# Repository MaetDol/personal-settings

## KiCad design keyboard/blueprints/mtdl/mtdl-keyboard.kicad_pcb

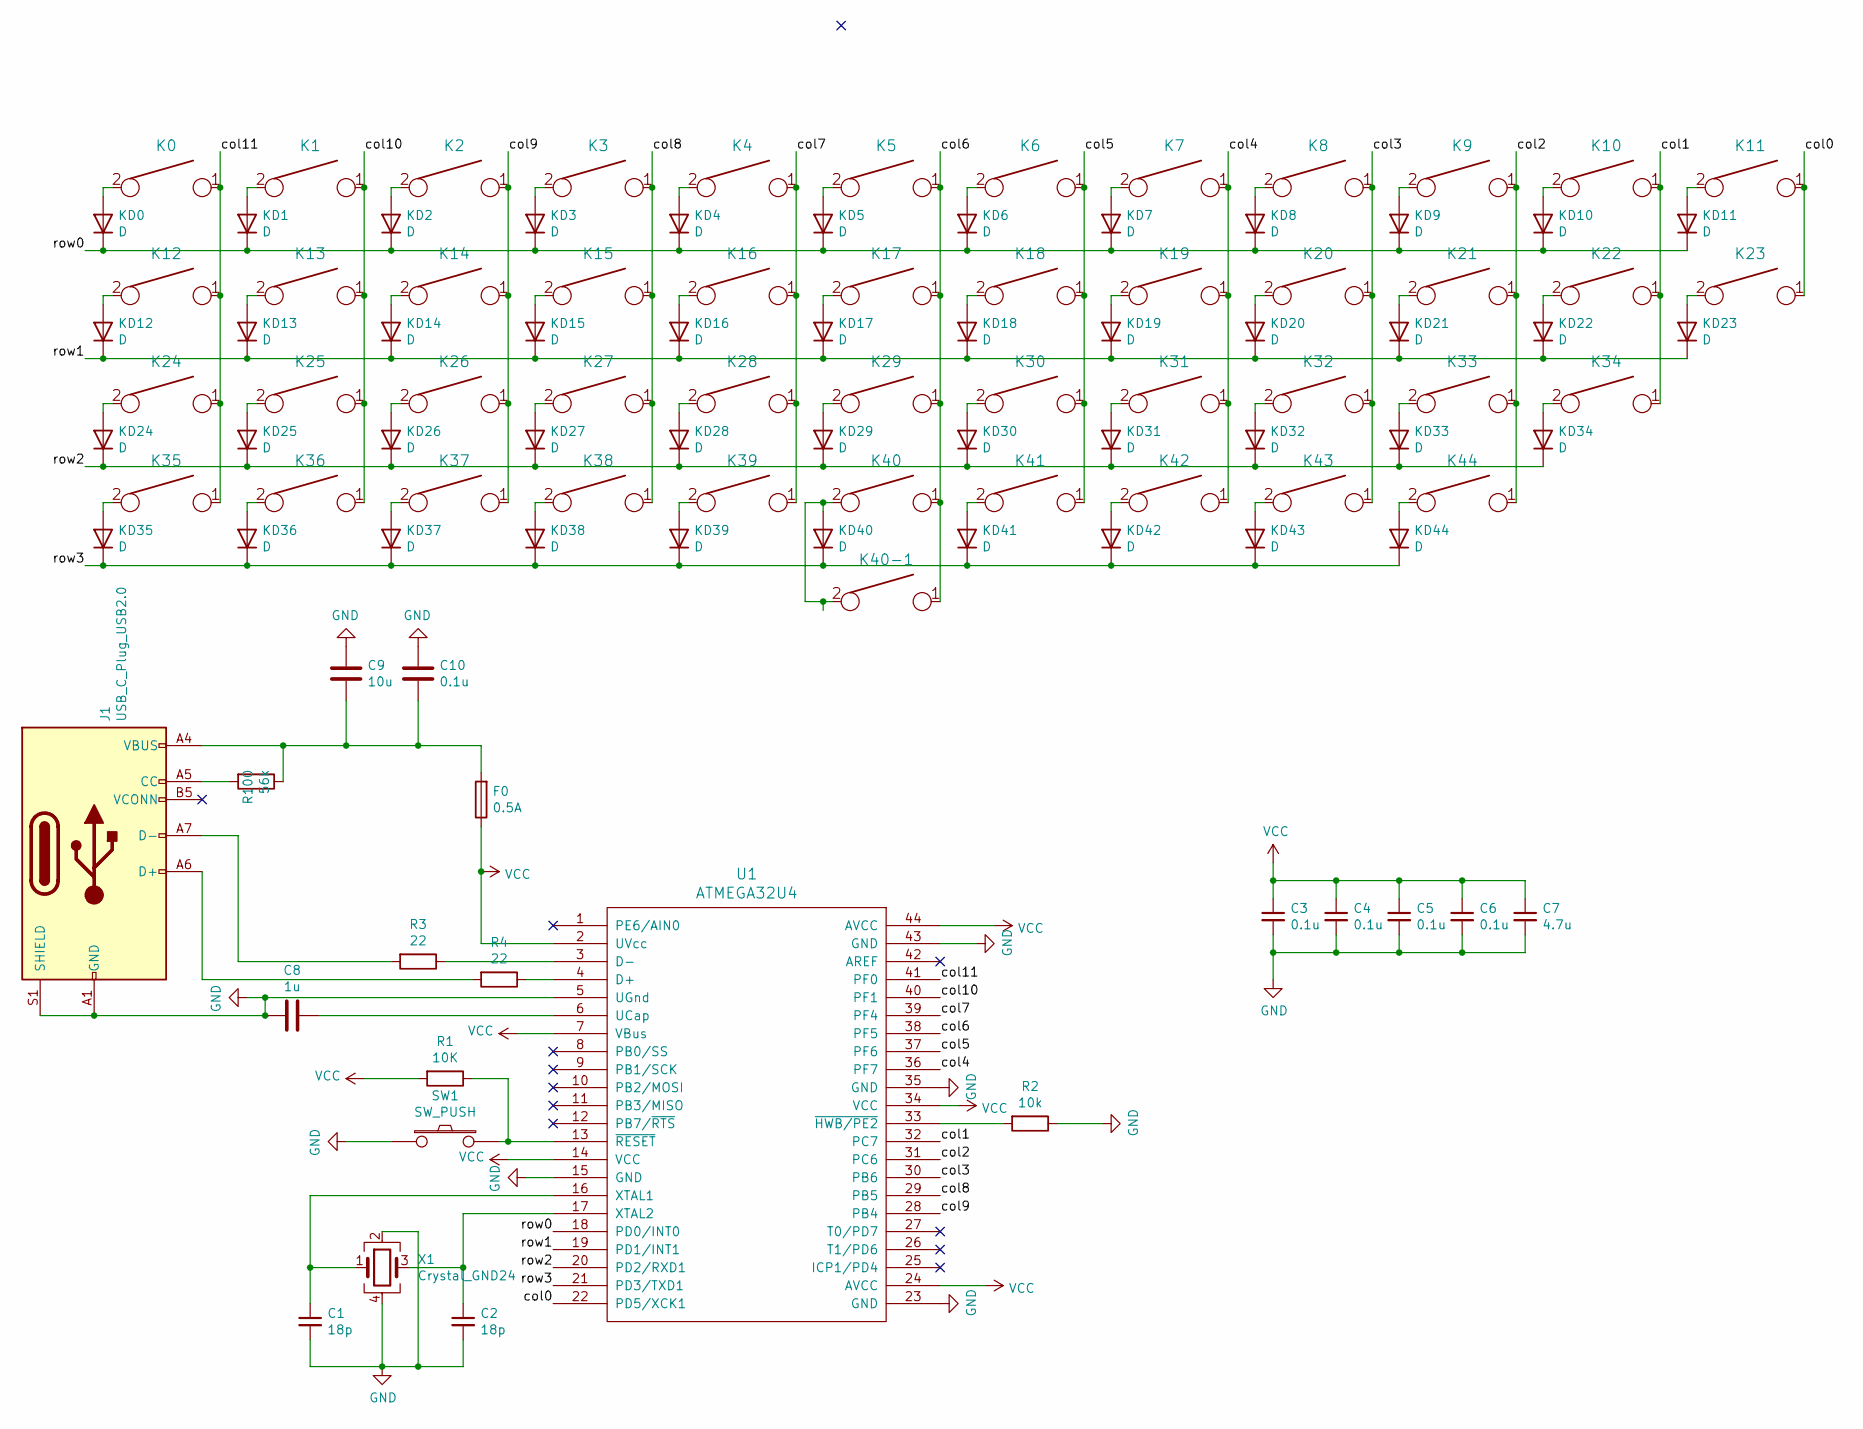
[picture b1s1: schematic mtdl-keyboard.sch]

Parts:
C1, C2: 18p; C_0805_2012Metric
C3, C4, C5, C6, C10: 0.1u; C_0805_2012Metric
C7: 4.7u; C_0805_2012Metric
C8: 1u; C_0805_2012Metric
C9: 10u; C_0805_2012Metric
F0: 0.5A; Fuse_0805_2012Metric
J1: USB_C_Plug_USB2.0; USB_C_Receptacle_Amphenol_12401548E4-2A
K0, K39, K40-1: KEYSW; Mx_Alps_200
K1, K2, K3, K4, K5, K6, K7, K8, K9, K10, K11, K13, K14, K15, K16, K17, K18, K19, K20, K21, K22, K25, K26, K27, K28, K29, K30, K31, K32, K33, K35, K37, K38, K42, K44: KEYSW; Mx_Alps_100
K12, K34: KEYSW; Mx_Alps_175
K23, K41, K43: KEYSW; Mx_Alps_125
K24: KEYSW; Mx_Alps_225
K36: KEYSW; Mx_Alps_150
K40: KEYSW; Mx_Alps_625
KD0, KD1, KD2, KD3, KD4, KD5, KD6, KD7, KD8, KD9, KD10, KD11, KD12, KD13, KD14, KD15, KD16, KD17, KD18, KD19, KD20, KD21, KD22, KD23, KD24, KD25, KD26, KD27, KD28, KD29, KD30, KD31, KD32, KD33, KD34, KD35, KD36, KD37, KD38, KD39, KD40, KD41, KD42, KD43, KD44: D; D_0805_2012Metric
R1: 10K; R_0805_2012Metric
R2: 10k; R_0805_2012Metric
R3, R4: 22; R_0805_2012Metric
R100: 56k; R_0805_2012Metric
SW1: SW_PUSH; SW_SPST_TL3342
U1: ATMEGA32U4; TQFP-44_10x10mm_P0.8mm
X1: Crystal_GND24; Crystal_SMD_TXC_7M-4Pin_3.2x2.5mm

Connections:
/col0: K0.1, K12.1, K24.1, K35.1, U1.41 (PF0)
/col1: K1.1, K13.1, K25.1, K36.1, U1.40 (PF1)
/col2: K2.1, K14.1, K26.1, K37.1, U1.28 (PB4)
/col3: K3.1, K15.1, K27.1, K38.1, U1.29 (PB5)
/col4: K4.1, K16.1, K28.1, K39.1, U1.39 (PF4)
/col5: K5.1, K17.1, K29.1, K40.1, K40-1.1, U1.38 (PF5)
/col6: K6.1, K18.1, K30.1, K41.1, U1.37 (PF6)
/col7: K7.1, K19.1, K31.1, K42.1, U1.36 (PF7)
/col8: K8.1, K20.1, K32.1, K43.1, U1.30 (PB6)
/col9: K9.1, K21.1, K33.1, K44.1, U1.31 (PC6)
/col10: K10.1, K22.1, K34.1, U1.32 (PC7)
/col11: K11.1, K23.1, U1.22 (PD5/XCK1)
/row0: KD0.1 (K), KD1.1 (K), KD2.1 (K), KD3.1 (K), KD4.1 (K), KD5.1 (K), KD6.1 (K), KD7.1 (K), KD8.1 (K), KD9.1 (K), KD10.1 (K), KD11.1 (K), U1.18 (PD0/INT0)
/row1: KD12.1 (K), KD13.1 (K), KD14.1 (K), KD15.1 (K), KD16.1 (K), KD17.1 (K), KD18.1 (K), KD19.1 (K), KD20.1 (K), KD21.1 (K), KD22.1 (K), KD23.1 (K), U1.19 (PD1/INT1)
/row2: KD24.1 (K), KD25.1 (K), KD26.1 (K), KD27.1 (K), KD28.1 (K), KD29.1 (K), KD30.1 (K), KD31.1 (K), KD32.1 (K), KD33.1 (K), KD34.1 (K), U1.20 (PD2/RXD1)
/row3: KD35.1 (K), KD36.1 (K), KD37.1 (K), KD38.1 (K), KD39.1 (K), KD40.1 (K), KD41.1 (K), KD42.1 (K), KD43.1 (K), KD44.1 (K), U1.21 (PD3/TXD1)
GND: C1.2, C2.2, C3.2, C4.2, C5.2, C6.2, C7.2, C8.2, C9.1, C10.1, J1.A1 (GND), J1.A12 (GND), J1.B1 (GND), J1.B12 (GND), J1.S1 (SHIELD), R2.1, SW1.1, U1.5 (UGnd), U1.15 (GND), U1.23 (GND), U1.35 (GND), U1.43 (GND), X1.2, X1.4
unnamed: C1.1, U1.16 (XTAL1), X1.1
unnamed: C2.1, U1.17 (XTAL2), X1.3
unnamed: C8.1, U1.6 (UCap)
unnamed: C9.2, C10.2, F0.2, J1.A4 (VBUS), J1.A9 (VBUS), J1.B4 (VBUS), J1.B9 (VBUS), R100.1
unnamed: J1.A5 (CC), R100.2
unnamed: J1.A6 (D+), R4.2
unnamed: J1.A7 (D-), R3.2
unnamed: K0.2, KD0.2 (A)
unnamed: K1.2, KD1.2 (A)
unnamed: K2.2, KD2.2 (A)
unnamed: K3.2, KD3.2 (A)
unnamed: K4.2, KD4.2 (A)
unnamed: K5.2, KD5.2 (A)
unnamed: K6.2, KD6.2 (A)
unnamed: K7.2, KD7.2 (A)
unnamed: K8.2, KD8.2 (A)
unnamed: K9.2, KD9.2 (A)
unnamed: K10.2, KD10.2 (A)
unnamed: K11.2, KD11.2 (A)
unnamed: K12.2, KD12.2 (A)
unnamed: K13.2, KD13.2 (A)
unnamed: K14.2, KD14.2 (A)
unnamed: K15.2, KD15.2 (A)
unnamed: K16.2, KD16.2 (A)
unnamed: K17.2, KD17.2 (A)
unnamed: K18.2, KD18.2 (A)
unnamed: K19.2, KD19.2 (A)
unnamed: K20.2, KD20.2 (A)
unnamed: K21.2, KD21.2 (A)
unnamed: K22.2, KD22.2 (A)
unnamed: K23.2, KD23.2 (A)
unnamed: K24.2, KD24.2 (A)
unnamed: K25.2, KD25.2 (A)
unnamed: K26.2, KD26.2 (A)
unnamed: K27.2, KD27.2 (A)
unnamed: K28.2, KD28.2 (A)
unnamed: K29.2, KD29.2 (A)
unnamed: K30.2, KD30.2 (A)
unnamed: K31.2, KD31.2 (A)
unnamed: K32.2, KD32.2 (A)
unnamed: K33.2, KD33.2 (A)
unnamed: K34.2, KD34.2 (A)
unnamed: K35.2, KD35.2 (A)
unnamed: K36.2, KD36.2 (A)
unnamed: K37.2, KD37.2 (A)
unnamed: K38.2, KD38.2 (A)
unnamed: K39.2, KD39.2 (A)
unnamed: K40.2, K40-1.2, KD40.2 (A)
unnamed: K41.2, KD41.2 (A)
unnamed: K42.2, KD42.2 (A)
unnamed: K43.2, KD43.2 (A)
unnamed: K44.2, KD44.2 (A)
unnamed: R1.1, SW1.2, U1.13 (~RESET)
unnamed: R2.2, U1.33 (~HWB/PE2)
unnamed: R3.1, U1.3 (D-)
unnamed: R4.1, U1.4 (D+)
VCC: C3.1, C4.1, C5.1, C6.1, C7.1, F0.1, R1.2, U1.2 (UVcc), U1.7 (VBus), U1.14 (VCC), U1.24 (AVCC), U1.34 (VCC), U1.44 (AVCC)

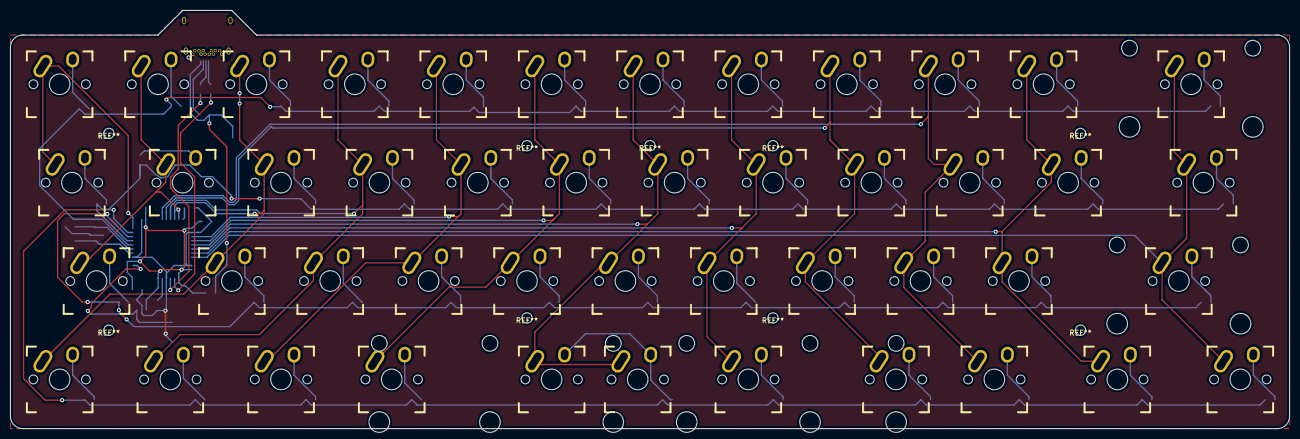
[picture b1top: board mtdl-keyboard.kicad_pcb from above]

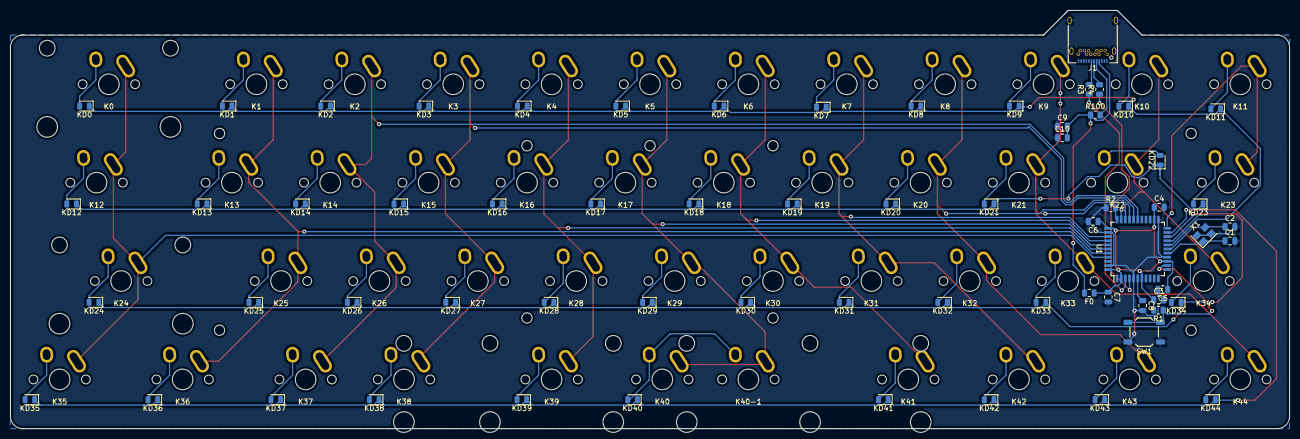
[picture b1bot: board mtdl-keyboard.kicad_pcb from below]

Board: 2 copper layers, 247.6 x 81.0 mm, 111 parts (65 on the bottom side), 74 nets.

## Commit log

2016-10-27 File Upload
2016-12-18 Update _vimrc
2017-02-27 Added settings for "Vundle"
2017-03-02 Add AutoComplPop setting
    오토컴플팝 플러그인 관련 세팅 - 탭으로 선택, 엔터로는 선택 안되게끔
    신택스, 컬러스킴 관련 설정 - 백그라운드 테마, 블랙으로 설정
2017-03-02 Deleted old version file
    이전 버전의 vimrc파일 삭제
2019-01-18 Private planck keymap
    Currently usage keymap for planck
2019-06-30 Added keymap file for planck rev6
2020-01-07 test commit
2020-06-03 Add git template file
2020-07-02 Added Quick guide for me
    Included way to install vundle and apply it
2020-07-03 Add using plugin
    vim-jsx-pretty plugin for jsx syntax highlight
    nerdtree plugin for show tree
2020-07-16 Update using plugins
    Add vim-closetag plugin with setting
2020-07-17 Set encoding utf8
    어떻게 이걸 잊을수가 있지?
2020-07-23 Add settings and change rule slightly
    설정해야할 것 예시 추가
2020-07-27 Modify keymap
    Add lower keymap - comma
2020-08-03 Delete NERDTree plugin
    Not used
2020-08-05 Simplify template!
    제목
    - 타입 : 오히려 Add인지, Create인지 구별하며 작성하면 부자연스러운 문장이 만들어지네요. 커밋 내용을 확실하게 정리할 수 있는 제목을 작성할 수 있게 노력해야겠습니다.
    - 넘버링 : 잘못 이해하고 있었습니다. 커밋 순서를 적는것이 아닌, 작업한 내용이 이슈와 관련있을때 해당 이슈의 번호를 적는거였네요.
    본문
    - 본문 길이를 나타내는 주석 위치 변경 : 커밋할때마다 맨 아래에 나오는 변경 내역이 커밋 작성하면서 참고하라고 나오는 줄 알았는데,
    해당 내역을 이용해 커밋 내용을 작성해야한
2020-08-21 변경사항 없음: 커밋내에서 마크다운 사용가능한지 확인용
    [테스트 링크](naver.com)
2020-09-01 Add option, settings
2020-09-21 SSH Test
2020-09-21 Test SSH via vscode
2021-02-19 Sync to rev6 keymap
    add comma to lower layer
2021-02-19 맨날 까먹고 헷갈려서 따로 기록해둡니다
    Planck 키보드 플래싱하기
2021-03-04 Add how to use this vimrc
    그리고 애매한 단어 수정
2021-03-04 Add missing quote
    and additional descript
2021-03-18 Add How to set PAT
2021-04-05 내용 보충 및 형식 변경
    윈도우, 리눅스에서 각각 플래싱 하는법으로 나눠서 기재
    트러블 슈팅 내용 기재
2021-04-05 Rename keymap directory
2021-04-05 Add 'Prt SC' key
    Use for screenshot
2021-07-11 ADD: MTDL 키보드 qmk 정보 파일 추가
2021-07-11 ADD: Set default layout macro
2021-07-12 Add rich_45 keymap
2021-07-12 Update ROWS and COLUMNS
2021-07-12 ADD: Qwerty, Lower, Raise keymap added
2021-07-12 Refactor: Create keyboard directory
2021-07-12 Create for dwg directory
    It's empty file
2021-07-12 Initial upload for plank_low.dwg
2021-07-12 Create mtdl.dwg
    Acrylic case but test version
2021-07-12 Rename flash.md to README.md
2021-07-13 Add mtdl working files
2021-07-13 Change case style to Banana Flavor!
    단차가 있고 노란색을 포인트로 준 하우징으로 변경
2021-07-16 FIx: 나사가 서로 교체하게하여 유지보수하기 편하게 변경함
    그리고 볼트의 크기도 변경했습니다
2024-03-16 Create .zshrc
    현재 셋업 백업
2024-03-16 Update .zshrc
    zsh 테마 관련 파일 다운 링크 추가
2024-12-19 headline 테마 파일 추가
2025-09-18 zsh-autosuggestion 설치법 추가
2025-09-18 add iterm profile
2025-09-18 볼드여도 잘 보여야지
    볼드일때 흰색처리되는 이슈 수정
